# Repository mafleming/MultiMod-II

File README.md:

HP-71B MultiMod II Repository

# MultiMod II, ROM and RAM Storage for the HP-71B

The MultiMod II is a follow-on development of the MultiMod ROM Emulator for the HP-71B handheld computer. The MultiMod was based on a Microchip PIC processor that stored ROM images in its flash memory and made those ROMs accessible to the HP-71B operator. However, the MultiMod could not provide RAM memory.

The MultiMod II is based on a Lattice iCE40UP5K FPGA with 128KB of single port RAM (SPRAM) and 15KB of dual port RAM. The FPGA fabric provides the logic needed to present the content of the SPRAM as a series of both ROM or RAM devices. The Winbond 16KB serial flash memory serves to hold up to four FPGA configuration bitstreams, and is also used to store ROM images that the HP-71B operator can dynamically plug and unplug into the HP-71B as needed.

# MultiMod II Board Design
The MultiMod II PCB is a four layer, two sided component design. The design was done in Kicad 9.0 and the design files can be found in the **board** directory.

# MultiMod II FPGA Configuration
To configure and provide content for ROM and RAM memories, a soft CPU is instantiated in fabric using the 15KB of dual port RAM for its programs. The J1a Forth CPU was selected in order to implement the intelligent functionality of the MultiMod II HP-71B accessory. The use of Forth as the base language complemented the availability of Forth for the HP-71B itself. The basis files can be found in the **mecrisp-ice-2.7** directory.

The mecrisp-ice project combines the J1a Forth CPU with the Mecrisp ANSI Forth implementation that targets the J1a instruction set. Details about the J1a implementation can be found at James Bowman's [github repository](https://github.com/jamesbowman/swapforth). More information about Mecrisp Forth can be found at its [Sourceforge](https://mecrisp.sourceforge.net/) site. [Unofficial documentation](https://mecrisp-stellaris-folkdoc.sourceforge.io/) for Mecrisp Forth can be found on Sourceforge as well.

This configuration was customized for two purposes; one configuration serves as a programmable bootloader when connected to a host, while the second is the production configuration when the MultiMod II is operating in the HP-71B.

## Bootloader Configuration
The bootloader Verilog and Forth files can be found in the **mmj1boot** subdirectory within the **mecrisp-ice** containing directory.

The bootloader configuration uses the standard mecrisp-ice j1a processor and USB device to communicate with a connected host. Going beyond the standard bootloader ability to update the production configuration, the interactive Forth console provides the means to transfer files and even extend its own capabilities.

## Production Configuration
The bootloader Verilog and Forth files can be found in the **multimod** subdirectory within the **mecrisp-ice** containing directory.

The production bitstream configuration replaces the mecrisp-ice USB device interface with a serial interface. The serial device data and control registers are mapped into the HP-71B address space so that the HP-71B can interact with the Forth console. This gives the HP-71B operator the ability to configure the MultiMod II, plugging and unplugging ROMs at will. Independent RAM (IRAM) device content can be saved to flash, allowing the operator to compose collections of programs that can be saved to flash and later loaded when needed. All the functional capability of an external storage device are provided by the MultiMod II.

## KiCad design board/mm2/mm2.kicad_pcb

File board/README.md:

# MultiMod-II Production Board Design
The Kicad design files and BOM for the MultiMod-II are contained here. An image of the board and its components appear below.

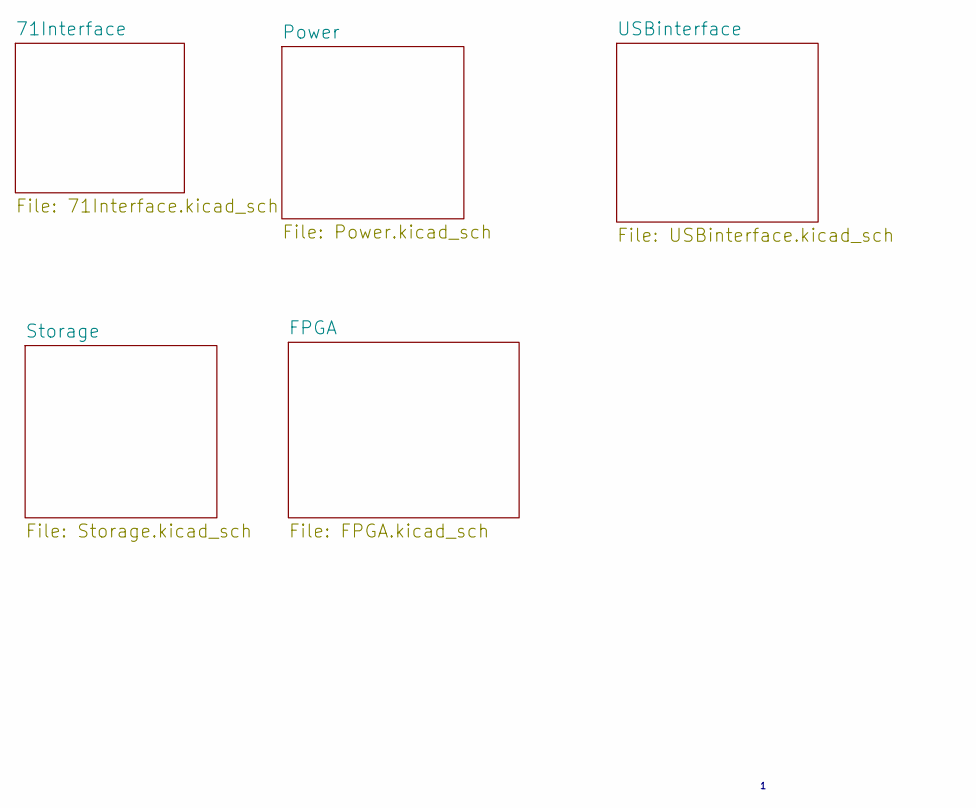
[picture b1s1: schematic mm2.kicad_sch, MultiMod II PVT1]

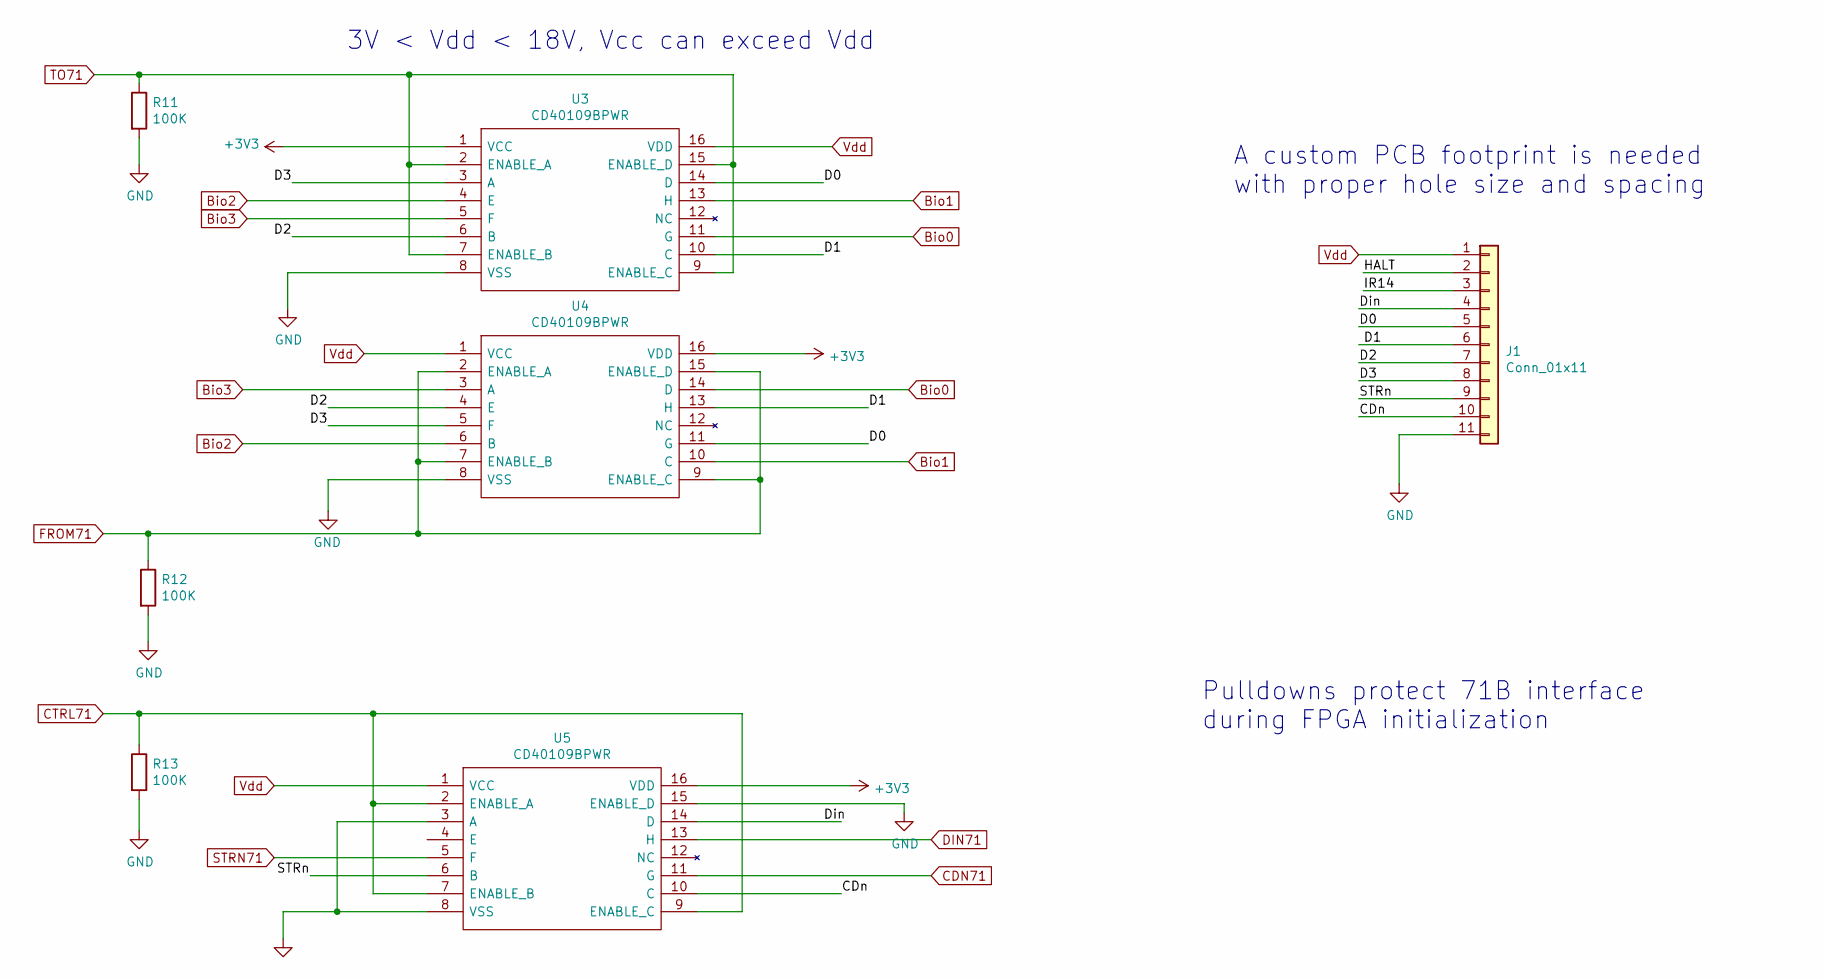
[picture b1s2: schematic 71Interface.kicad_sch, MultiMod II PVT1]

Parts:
J1: Conn_01x11; SIP-11
R11, R12, R13: 100K; R_0603_1608Metric
U3, U4, U5: CD40109BPWR; TSSOP-16_4.4x5mm_P0.65mm; Mouser2 Part Number 595-CD40109BPWR

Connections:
+3V3: U3.1 (VCC), U4.16 (VDD), U5.16 (VDD); also elsewhere on the board
/71Interface/CDn: J1.10, U5.10 (C)
/71Interface/D0: J1.5, U3.14 (D), U4.11 (G)
/71Interface/D1: J1.6, U3.10 (C), U4.13 (H)
/71Interface/D2: J1.7, U3.6 (B), U4.4 (E)
/71Interface/D3: J1.8, U3.3 (A), U4.5 (F)
/71Interface/Din: J1.4, U5.14 (D)
/71Interface/HALT: J1.2
/71Interface/IR14: J1.3
/71Interface/STRn: J1.9, U5.6 (B)
Bio0: U3.11 (G), U4.14 (D); also elsewhere on the board
Bio1: U3.13 (H), U4.10 (C); also elsewhere on the board
Bio2: U3.4 (E), U4.6 (B); also elsewhere on the board
Bio3: U3.5 (F), U4.3 (A); also elsewhere on the board
CDN71: U5.11 (G); also elsewhere on the board
CTRL71: R13.1, U5.2 (ENABLE_A), U5.7 (ENABLE_B), U5.9 (ENABLE_C); also elsewhere on the board
DIN71: U5.13 (H); also elsewhere on the board
FROM71: R12.1, U4.2 (ENABLE_A), U4.7 (ENABLE_B), U4.9 (ENABLE_C), U4.15 (ENABLE_D); also elsewhere on the board
GND: J1.11, R11.2, R12.2, R13.2, U3.8 (VSS), U4.8 (VSS), U5.3 (A), U5.8 (VSS), U5.15 (ENABLE_D); also elsewhere on the board
STRN71: U5.5 (F); also elsewhere on the board
TO71: R11.1, U3.2 (ENABLE_A), U3.7 (ENABLE_B), U3.9 (ENABLE_C), U3.15 (ENABLE_D); also elsewhere on the board
Vdd: J1.1, U3.16 (VDD), U4.1 (VCC), U5.1 (VCC); also elsewhere on the board

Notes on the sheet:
A custom PCB footprint is needed with proper hole size and spacing
Pulldowns protect 71B interface during FPGA initialization
3V < Vdd < 18V, Vcc can exceed Vdd

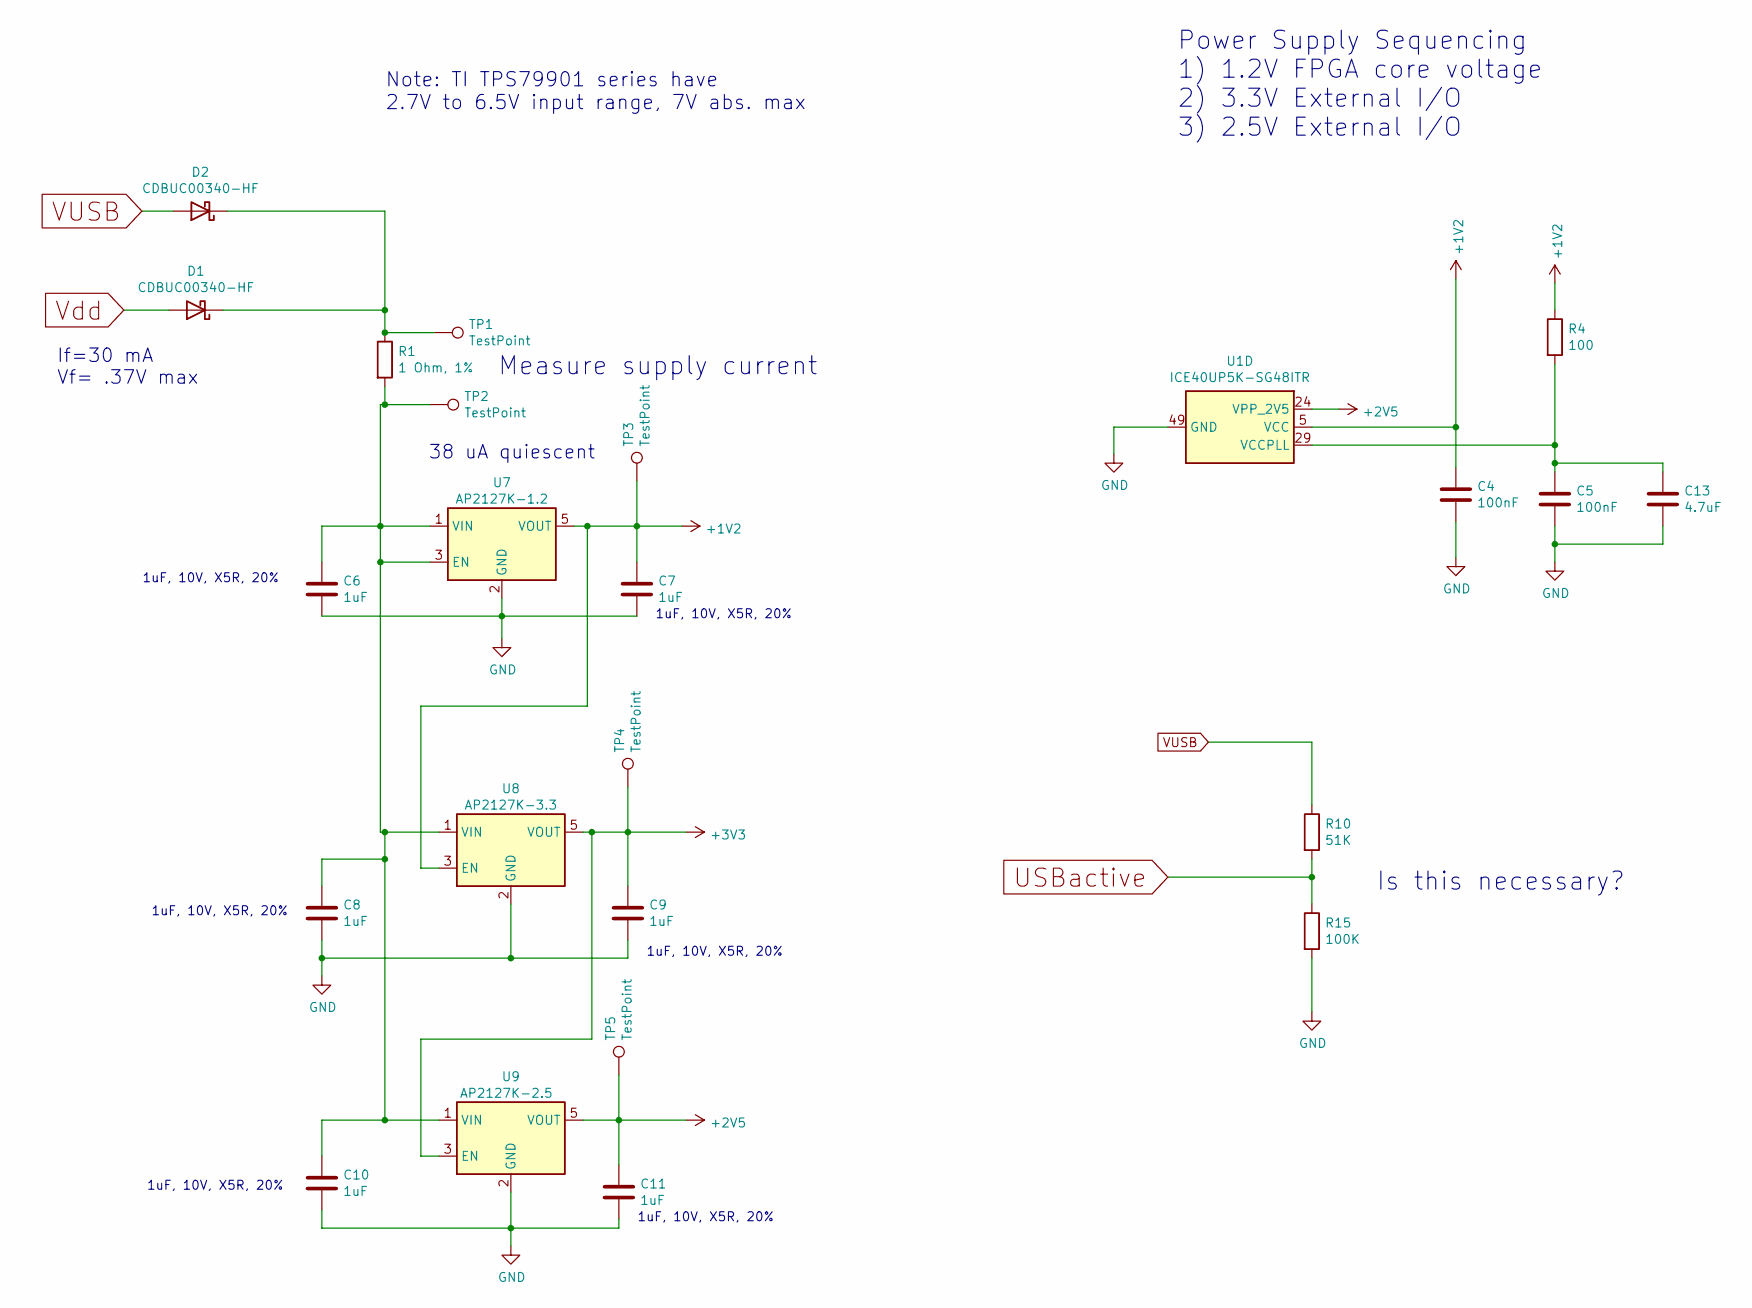
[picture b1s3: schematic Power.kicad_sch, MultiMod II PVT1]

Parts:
C4, C5: 100nF; C_0603_1608Metric
C6, C7, C8, C9, C10, C11: 1uF; C_0603_1608Metric
C13: 4.7uF; C_0603_1608Metric
D1, D2: CDBUC00340-HF; D_0603_1608Metric
R1: 1 Ohm, 1%; R_0603_1608Metric
R4: 100; R_0603_1608Metric
R10: 51K; R_0603_1608Metric
R15: 100K; R_0603_1608Metric
TP1, TP2, TP3, TP4, TP5: TestPoint; TestPoint_Pad_1.0x1.0mm
U1: ICE40UP5K-SG48ITR; QFN-48-1EP_7x7mm_P0.5mm_EP5.6x5.6mm
U7: AP2127K-1.2; SOT-23-5
U8: AP2127K-3.3; SOT-23-5
U9: AP2127K-2.5; SOT-23-5

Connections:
+1V2: C4.1, C7.1, R4.1, TP3.1, U1.5 (VCC), U1.30 (VCC), U7.5 (VOUT), U8.3 (EN)
+2V5: C11.1, TP5.1, U1.24 (VPP_2V5), U9.5 (VOUT)
+3V3: C9.1, TP4.1, U8.5 (VOUT), U9.3 (EN); also elsewhere on the board
GND: C4.2, C5.2, C6.2, C7.2, C8.2, C9.2, C10.2, C11.2, C13.2, R15.2, U1.49 (GND), U7.2 (GND), U8.2 (GND), U9.2 (GND); also elsewhere on the board
unnamed: D1.1 (K), D2.1 (K), R1.1, TP1.1
unnamed: C5.1, C13.1, R4.2, U1.29 (VCCPLL)
unnamed: C6.1, C8.1, C10.1, R1.2, TP2.1, U7.1 (VIN), U7.3 (EN), U8.1 (VIN), U9.1 (VIN)
USBactive: R10.2, R15.1; also elsewhere on the board
VUSB: D2.2 (A), R10.1; also elsewhere on the board
Vdd: D1.2 (A); also elsewhere on the board

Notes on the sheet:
1uF, 10V, X5R, 20%
Measure supply current
Power Supply Sequencing 1) 1.2V FPGA core voltage 2) 3.3V External I/O 3) 2.5V External I/O
Note: TI TPS79901 series have 2.7V to 6.5V input range, 7V abs. max
Is this necessary?
If=30 mA Vf= .37V max
38 uA quiescent

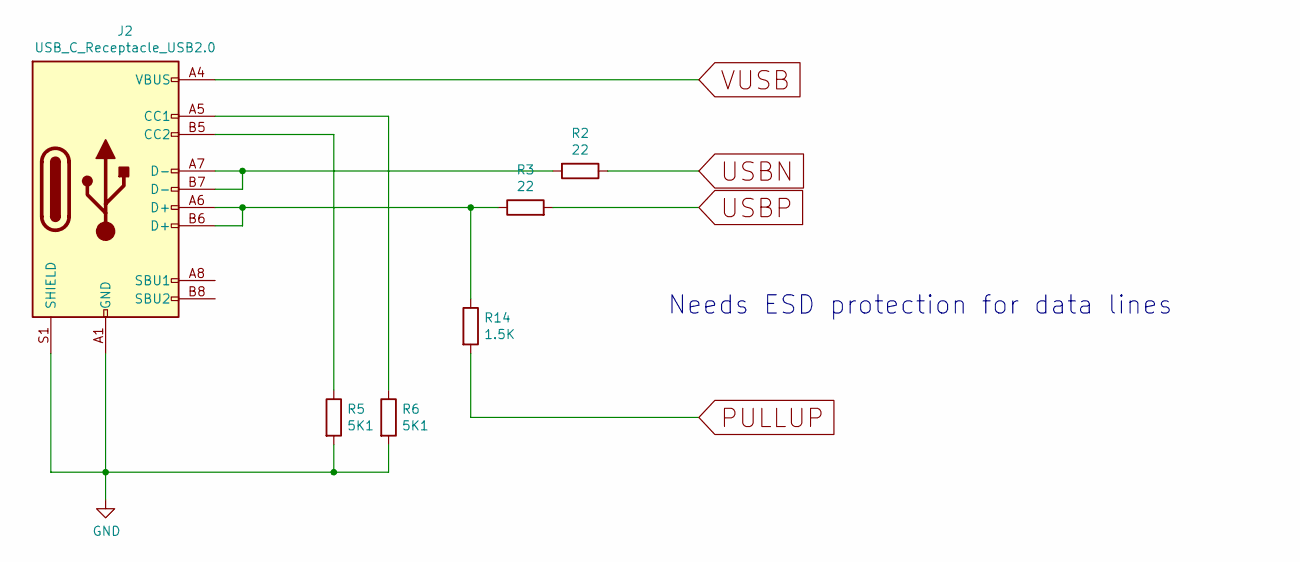
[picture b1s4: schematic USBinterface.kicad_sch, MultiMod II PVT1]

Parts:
J2: USB_C_Receptacle_USB2.0; USB_C_Receptacle_JAE_DX07S016JA1R1500
R2, R3: 22; R_0603_1608Metric
R5, R6: 5K1; R_0603_1608Metric
R14: 1.5K; R_0603_1608Metric

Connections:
GND: J2.A1 (GND), J2.A12 (GND), J2.B1 (GND), J2.B12 (GND), J2.S1 (SHIELD), R5.2, R6.2; also elsewhere on the board
unnamed: J2.A5 (CC1), R6.1
unnamed: J2.B5 (CC2), R5.1
unnamed: J2.A6 (D+), J2.B6 (D+), R3.1, R14.1
unnamed: J2.A7 (D-), J2.B7 (D-), R2.2
PULLUP: R14.2; also elsewhere on the board
USBN: R2.1; also elsewhere on the board
USBP: R3.2; also elsewhere on the board
VUSB: J2.A4 (VBUS), J2.A9 (VBUS), J2.B4 (VBUS), J2.B9 (VBUS); also elsewhere on the board

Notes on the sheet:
Needs ESD protection for data lines

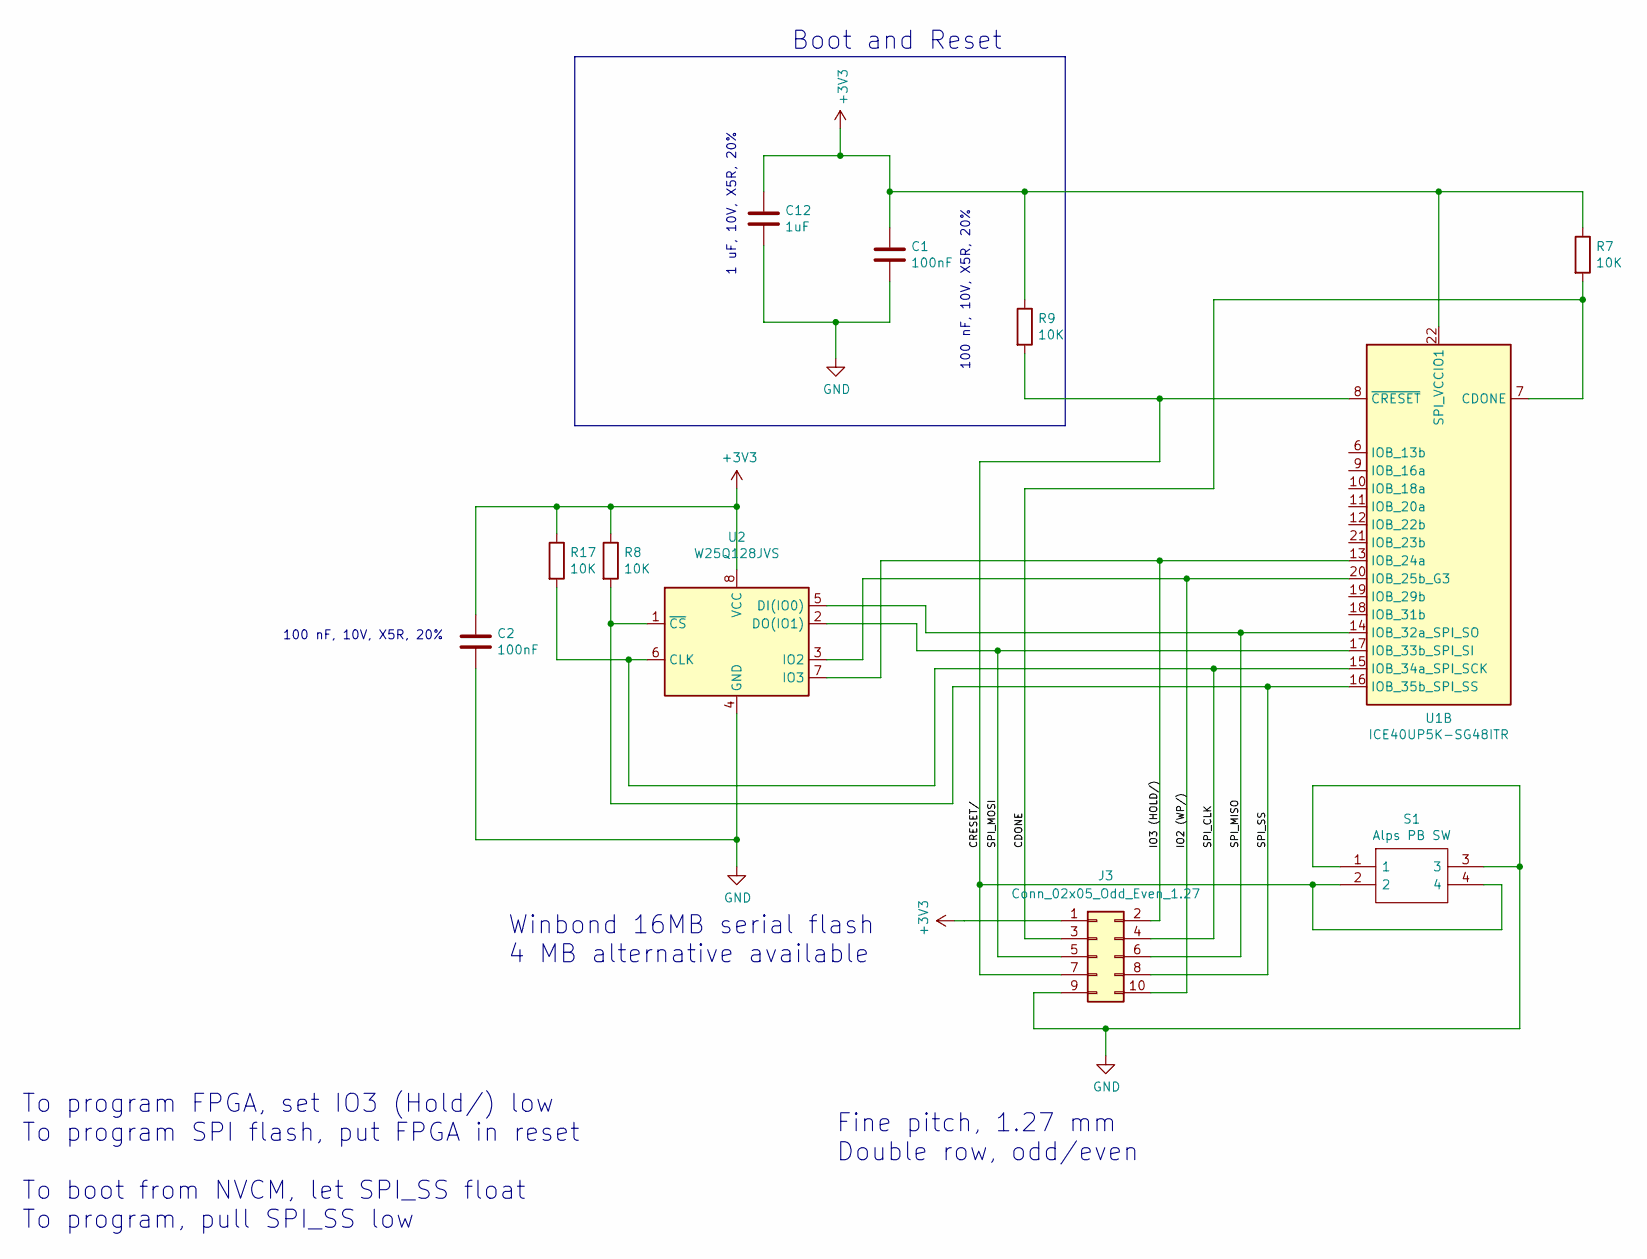
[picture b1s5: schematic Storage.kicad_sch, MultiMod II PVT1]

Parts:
C1, C2: 100nF; C_0603_1608Metric
C12: 1uF; C_0603_1608Metric
J3: Conn_02x05_Odd_Even_1.27; PinHeader_2x05_P1.27mm_Vertical
R7, R8, R9, R17: 10K; R_0603_1608Metric
S1: Alps PB SW; SKSVCBE010; Manufacturer_Part_Number SKSVCBE010
U1: ICE40UP5K-SG48ITR; QFN-48-1EP_7x7mm_P0.5mm_EP5.6x5.6mm
U2: W25Q128JVS; SOIC-8_5.23x5.23mm_P1.27mm

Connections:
+3V3: C1.1, C2.1, C12.1, J3.1, R7.1, R8.1, R9.1, R17.1, U1.22 (SPI_VCCIO1), U2.8 (VCC); also elsewhere on the board
/Storage/CDONE: J3.3, R7.2, U1.7 (CDONE)
/Storage/CRESET/: J3.7, R9.2, S1.2, S1.4, U1.8 (~CRESET)
/Storage/IO2 (WP/): J3.10, U1.20 (IOB_25b_G3), U2.3 (IO2)
/Storage/IO3 (HOLD/): J3.2, U1.13 (IOB_24a), U2.7 (IO3)
/Storage/SPI_CLK: J3.4, R17.2, U1.15 (IOB_34a_SPI_SCK), U2.6 (CLK)
/Storage/SPI_MISO: J3.6, U1.14 (IOB_32a_SPI_SO), U2.5 (DI(IO0))
/Storage/SPI_MOSI: J3.5, U1.17 (IOB_33b_SPI_SI), U2.2 (DO(IO1))
/Storage/SPI_SS: J3.8, R8.2, U1.16 (IOB_35b_SPI_SS), U2.1 (~CS)
GND: C1.2, C2.2, C12.2, J3.9, S1.1, S1.3, U2.4 (GND); also elsewhere on the board

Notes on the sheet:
Fine pitch, 1.27 mm Double row, odd/even
1 uF, 10V, X5R, 20%
Boot and Reset
100 nF, 10V, X5R, 20%
Winbond 16MB serial flash 4 MB alternative available
To program FPGA, set IO3 (Hold/) low To program SPI flash, put FPGA in reset To boot from NVCM, let SPI_SS float To program, pull SPI_SS low

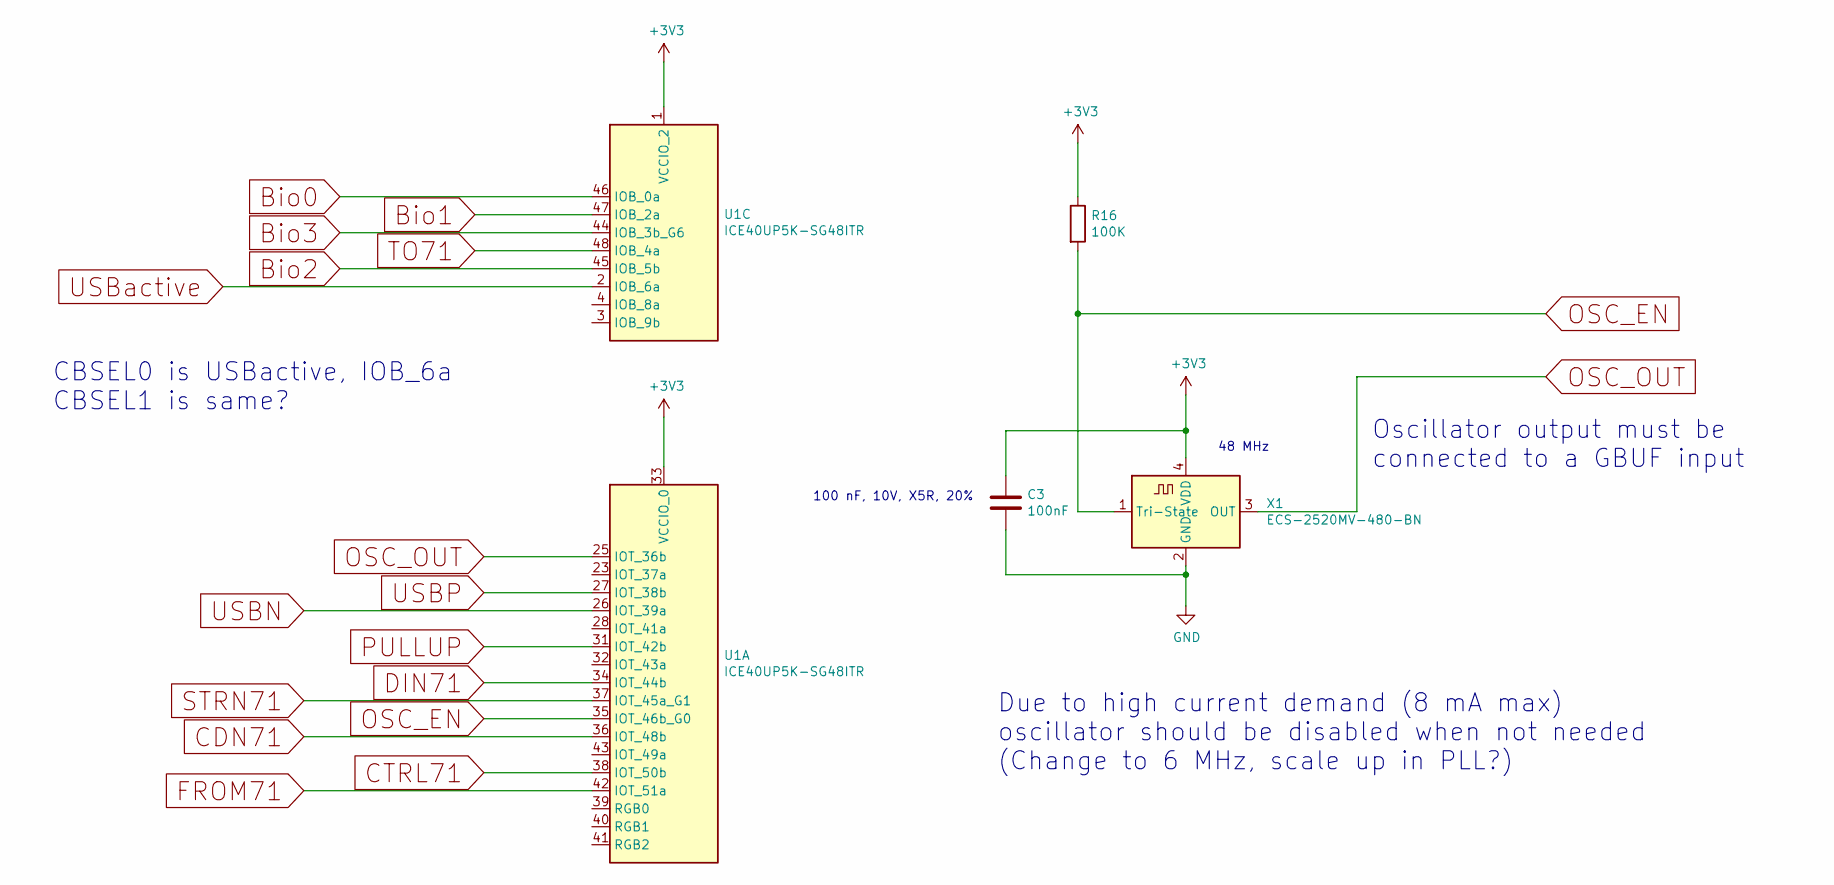
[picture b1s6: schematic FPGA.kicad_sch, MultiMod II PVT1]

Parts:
C3: 100nF; C_0603_1608Metric
R16: 100K; R_0603_1608Metric
U1: ICE40UP5K-SG48ITR; QFN-48-1EP_7x7mm_P0.5mm_EP5.6x5.6mm
X1: ECS-2520MV-480-BN; Oscillator_SMD_ECS_2520MV-xxx-xx-4Pin_2.5x2.0mm

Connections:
+3V3: C3.1, R16.1, U1.1 (VCCIO_2), U1.33 (VCCIO_0), X1.4 (VDD); also elsewhere on the board
Bio0: U1.46 (IOB_0a); also elsewhere on the board
Bio1: U1.47 (IOB_2a); also elsewhere on the board
Bio2: U1.45 (IOB_5b); also elsewhere on the board
Bio3: U1.44 (IOB_3b_G6); also elsewhere on the board
CDN71: U1.36 (IOT_48b); also elsewhere on the board
CTRL71: U1.38 (IOT_50b); also elsewhere on the board
DIN71: U1.34 (IOT_44b); also elsewhere on the board
FROM71: U1.42 (IOT_51a); also elsewhere on the board
GND: C3.2, X1.2 (GND); also elsewhere on the board
OSC_EN: R16.2, U1.35 (IOT_46b_G0), X1.1 (Tri-State)
OSC_OUT: U1.25 (IOT_36b), X1.3 (OUT)
PULLUP: U1.31 (IOT_42b); also elsewhere on the board
STRN71: U1.37 (IOT_45a_G1); also elsewhere on the board
TO71: U1.48 (IOB_4a); also elsewhere on the board
USBN: U1.26 (IOT_39a); also elsewhere on the board
USBP: U1.27 (IOT_38b); also elsewhere on the board
USBactive: U1.2 (IOB_6a); also elsewhere on the board

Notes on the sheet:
Oscillator output must be connected to a GBUF input
CBSEL0 is USBactive, IOB_6a CBSEL1 is same?
48 MHz
Due to high current demand (8 mA max) oscillator should be disabled when not needed (Change to 6 MHz, scale up in PLL?)
100 nF, 10V, X5R, 20%

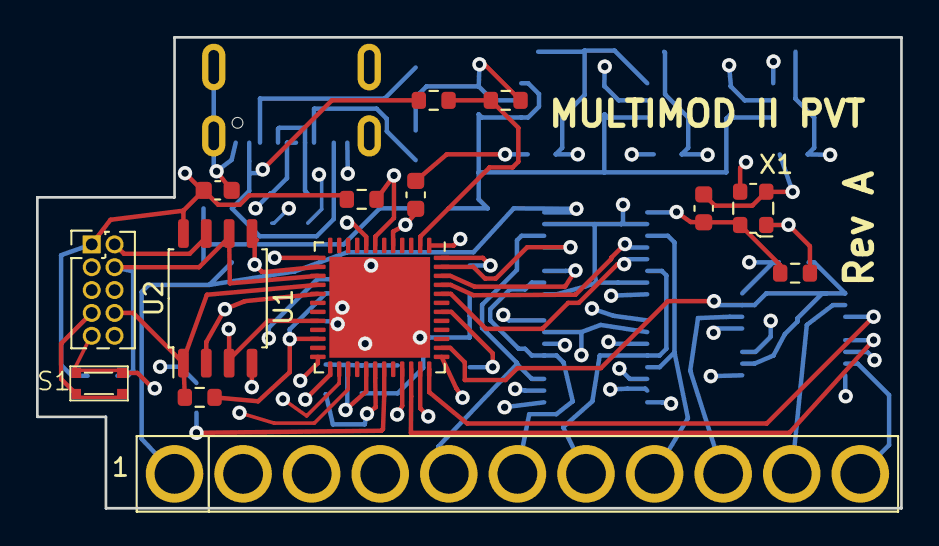
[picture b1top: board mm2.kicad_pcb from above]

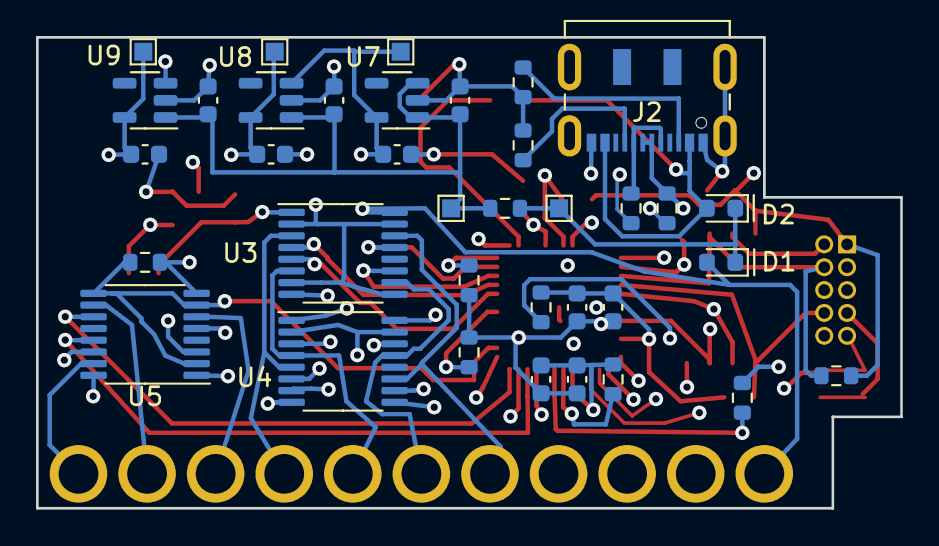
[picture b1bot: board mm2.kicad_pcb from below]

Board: 4 copper layers, 48.0 x 26.2 mm, 50 parts (36 on the bottom side), 44 nets.

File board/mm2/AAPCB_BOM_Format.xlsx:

Best Practice Bill of Materials (BOM) Template
1. Reference Designators - Place all designators with the same part number in o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
2. Description Value Package - Advanced Assembly's system perfers this to be co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
3. Alternate Part Numbers - Place in additional columns to the right on the sam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
4. Do Not Install (DNI) Parts - Indicate quantity zero and/or add DNI column
5. Notes - Place in additional column on the same line
6. Refrain from using merged cells
7. Mfg - If you require a specific manufacturer, specify here
*Please contact your account executive with any questions.*
 |  |  |  | êAuto-populates as you fill in the previous cellsê
Mfg Part # | Description | Value | Pkg | Description Value Pkg *AAPCB Format* | Ref. Des. | Qty | DNI | Notes | Mfg (Optional) | Vendor (Optional) | Vendor Part # (Optional) | Alternate Mfg Part # (Optional) | Type (Optional)
C1608X5R1A105M080AC | CAP CER | 100 nF 10V X5R 20% | 0603 SMD |  | C1, C2, C3, C4, C5 | 5 |  |  | TDK | Mouser
885012106010' | CAP CER | 1 uF 10V X5R 20% | 0603 SMD | CAP CER 1 uF 10V X5R 20% 0603 SMD | C6, C7, C8, C9, C10, C11, C12 | 7 |  |  | WURTH | Mouser
CGB3B1X5R1A475M055AC | CAP CER | 4.7 uF 10V X5R 20% | 0603 SMD | CAP CER 4.7 uF 10V X5R 20% 0603 SMD | C13 | 1 |  | EOL | TDK | Mouser
CDBU00340 | SCHOTTKY DIODE | 30mA 40V | 0603 SMD | SCHOTTKY DIODE 30mA 40V 0603 SMD | D1, D2 | 2 |  |  | COMCHIP | Mouser
DX07S016JA1R1500 | USB CONNECTOR |  |  | USB CONNECTOR | J2 | 1 |  |  | JAE | Mouser
20021111-00010T4LF | PIN HEADER | 2x5 1.27 MM PITCH |  | PIN HEADER 2x5 1.27 MM PITCH | J3 | 1 |  |  |  | Digi-Key
ERJ-3RSFR10V | RES | 0.1 OHM CURR SENSE | 0603 SMD | RES 0.1 OHM CURR SENSE 0603 SMD | R1 | 1 |  |  |  | Mouser
CPF0603F2R21C1 | RES | 22 OHM 1% | 0603 SMD | RES 22 OHM 1% 0603 SMD | R2, R3 | 2 |  |  |  | Mouser
CPF0603F100RC1 | RES | 100 OHM 1% | 0603 SMD | RES 100 OHM 1% 0603 SMD | R4 | 1 |  |  |  | Mouser
CPF0603F5K11C1 | RES | 5.1K OHM 1% | 0603 SMD | RES 5.1K OHM 1% 0603 SMD | R5, R6 | 2 |  |  |  | Mouser
5-1879337-9 | RES | 10K OHM 1% | 0603 SMD | RES 10K OHM 1% 0603 SMD | R7, R8, R9 | 3 |  |  |  | Mouser
CPF0603F49K9C1 | RES | 49.9K OHM 1% | 0603 SMD | RES 49.9K OHM 1% 0603 SMD | R10 | 1 |  |  |  | Mouser
CPF0603F100KC1 | RES | 100K OHM 1% | 0603 SMD | RES 100K OHM 1% 0603 SMD | R11, R12, R13, R15 | 4 |  |  |  | Mouser
SKSVCBE010 | SWITCH | TACTILE | SMD | SWITCH TACTILE SMD | S1 | 1 |  |  | ALPS | Mouser
ICE40UP5K-SG48I | LATTICE FPGA | ICE40 ULTRA PLUS | QFN-48 | LATTICE FPGA ICE40 ULTRA PLUS QFN-48 | U1 | 1 |  |  | LATTICE | Mouser
W25Q128JVS | SPI FLASH | 16 MB | SOIC-8 | SPI FLASH 16 MB SOIC-8 | U2 | 1 |  |  | WINBOND | Mouser
CD40109BPWR | LEVEL SHIFTER | QUAD L-H | TSSOP-16 | LEVEL SHIFTER QUAD L-H TSSOP-16 | U3, U4, U5 | 3 |  |  | TI | Mouser
AP2127K-1.2TRG1 | LDO REGULATOR | 1.2V 300mA | SOT-23-5 SMD | LDO REGULATOR 1.2V 300mA SOT-23-5 SMD | U7 | 1 |  |  | DIODES INC | Mouser
AP2127K-3.3TRG1 | LDO REGULATOR | 3.3V 300mA | SOT-23-5 SMD | LDO REGULATOR 3.3V 300mA SOT-23-5 SMD | U8 | 1 |  |  | DIODES INC | Mouser
AP2127K-2.5TRG1 | LDO REGULATOR | 2.5V 300mA | SOT-23-5 SMD | LDO REGULATOR 2.5V 300mA SOT-23-5 SMD | U9 | 1 |  |  | DIODES INC | Mouser
ECS-2520MV-480-DN-TR | CLOCK OSC | 48 MHZ | SMD | CLOCK OSC 48 MHZ SMD | X1 | 1 |  |  | ECS | Mouser

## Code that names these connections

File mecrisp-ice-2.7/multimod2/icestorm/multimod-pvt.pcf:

set_io rgb0 39
set_io rgb1 40
set_io rgb2 41

set_io data_0 46
set_io data_1 47
set_io data_2 45
set_io data_3 44

set_io to71   48
set_io from71 42
set_io ctrl71 38

set_io din71  34
set_io cdn71  36
set_io strn71 37

set_io spi_mosi 14
set_io spi_miso 17
set_io spi_clk  15
set_io spi_io2  20
set_io spi_io3  13
set_io spi_cs   16

set_io usb_dn    26
set_io usb_dp    27
set_io usb_dp_pu 31
set_io usb_activ  2

set_io clki    25
set_io clki_en 35

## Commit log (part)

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2026-05-27 MultiMod II Board Design Files
    Finished Kicad design files and BOM.
2026-06-01 MultiMod II Bootloader Using Mecrisp-ice
    This is version 2.7 of mecrisp-ice, an enhancement of James Bowman's J1A Forth CPU and Swapforth. Subdirectories for ports to other boards have been removed.
2026-06-01 Added Bootloader README.md
    Text taken from the Notes intro.
2026-06-06 Added Flash Security
    Words to lock or unlock 4KB blocks for write protection. Keep the bootloader safe!
2026-06-10 Auto stash before revert of "Added Flash Security"
2026-06-14 Documentation Updates
    Added notes for flash security. Changed name reference for pcf file from evt2 to pvt.
2026-06-15 Simplified Bootloader J1A CPU
    Much simpler addressing scheme with no unrelated HP-71B design references. Clean Verilog synthesis.
